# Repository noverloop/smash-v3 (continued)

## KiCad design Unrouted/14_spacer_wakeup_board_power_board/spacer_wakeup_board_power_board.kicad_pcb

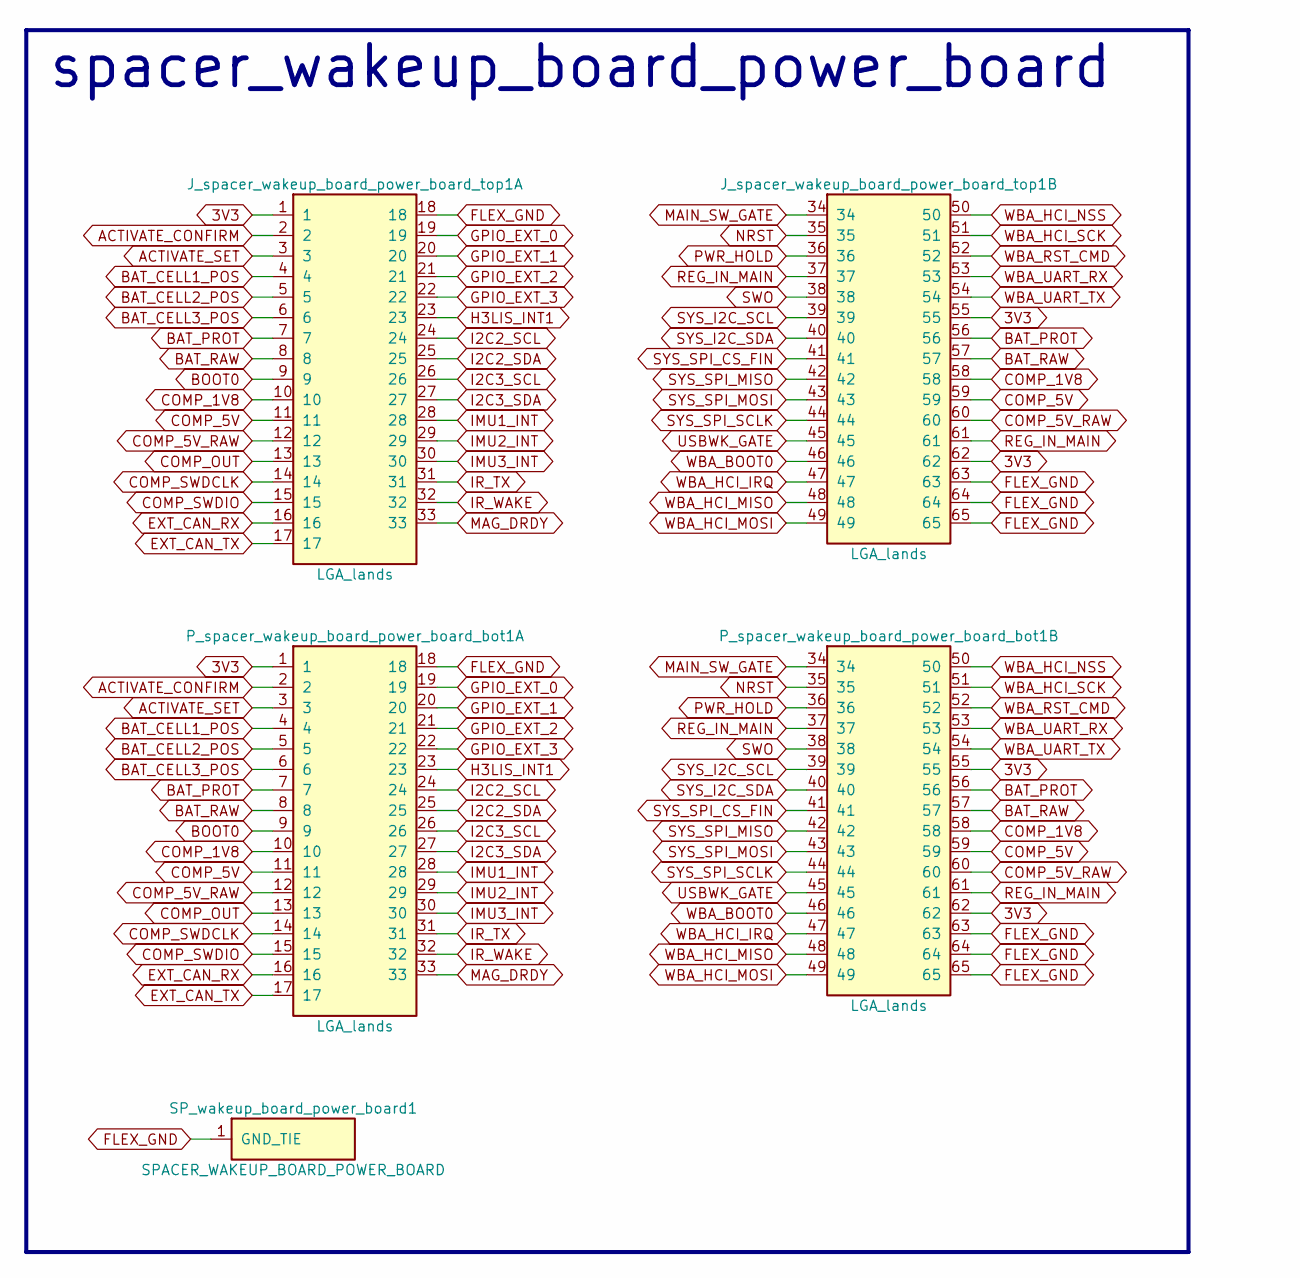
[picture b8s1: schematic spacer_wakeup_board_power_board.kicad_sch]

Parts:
J_spacer_wakeup_board_power_board_top1: LGA_lands; J_spacer_wakeup_board_power_board_top; MPN LGA_lands
P_spacer_wakeup_board_power_board_bot1: LGA_lands; P_spacer_wakeup_board_power_board_bot; MPN LGA_lands
SP_wakeup_board_power_board1: SPACER_WAKEUP_BOARD_POWER_BOARD; Spacer_Mechanical_34mm

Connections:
3V3: J_spacer_wakeup_board_power_board_top1.1, J_spacer_wakeup_board_power_board_top1.55, J_spacer_wakeup_board_power_board_top1.62, P_spacer_wakeup_board_power_board_bot1.1, P_spacer_wakeup_board_power_board_bot1.55, P_spacer_wakeup_board_power_board_bot1.62
ACTIVATE_CONFIRM: J_spacer_wakeup_board_power_board_top1.2, P_spacer_wakeup_board_power_board_bot1.2
ACTIVATE_SET: J_spacer_wakeup_board_power_board_top1.3, P_spacer_wakeup_board_power_board_bot1.3
BAT_CELL1_POS: J_spacer_wakeup_board_power_board_top1.4, P_spacer_wakeup_board_power_board_bot1.4
BAT_CELL2_POS: J_spacer_wakeup_board_power_board_top1.5, P_spacer_wakeup_board_power_board_bot1.5
BAT_CELL3_POS: J_spacer_wakeup_board_power_board_top1.6, P_spacer_wakeup_board_power_board_bot1.6
BAT_PROT: J_spacer_wakeup_board_power_board_top1.7, J_spacer_wakeup_board_power_board_top1.56, P_spacer_wakeup_board_power_board_bot1.7, P_spacer_wakeup_board_power_board_bot1.56
BAT_RAW: J_spacer_wakeup_board_power_board_top1.8, J_spacer_wakeup_board_power_board_top1.57, P_spacer_wakeup_board_power_board_bot1.8, P_spacer_wakeup_board_power_board_bot1.57
BOOT0: J_spacer_wakeup_board_power_board_top1.9, P_spacer_wakeup_board_power_board_bot1.9
COMP_1V8: J_spacer_wakeup_board_power_board_top1.10, J_spacer_wakeup_board_power_board_top1.58, P_spacer_wakeup_board_power_board_bot1.10, P_spacer_wakeup_board_power_board_bot1.58
COMP_5V: J_spacer_wakeup_board_power_board_top1.11, J_spacer_wakeup_board_power_board_top1.59, P_spacer_wakeup_board_power_board_bot1.11, P_spacer_wakeup_board_power_board_bot1.59
COMP_5V_RAW: J_spacer_wakeup_board_power_board_top1.12, J_spacer_wakeup_board_power_board_top1.60, P_spacer_wakeup_board_power_board_bot1.12, P_spacer_wakeup_board_power_board_bot1.60
COMP_OUT: J_spacer_wakeup_board_power_board_top1.13, P_spacer_wakeup_board_power_board_bot1.13
COMP_SWDCLK: J_spacer_wakeup_board_power_board_top1.14, P_spacer_wakeup_board_power_board_bot1.14
COMP_SWDIO: J_spacer_wakeup_board_power_board_top1.15, P_spacer_wakeup_board_power_board_bot1.15
EXT_CAN_RX: J_spacer_wakeup_board_power_board_top1.16, P_spacer_wakeup_board_power_board_bot1.16
EXT_CAN_TX: J_spacer_wakeup_board_power_board_top1.17, P_spacer_wakeup_board_power_board_bot1.17
FLEX_GND: J_spacer_wakeup_board_power_board_top1.18, J_spacer_wakeup_board_power_board_top1.63, J_spacer_wakeup_board_power_board_top1.64, J_spacer_wakeup_board_power_board_top1.65, P_spacer_wakeup_board_power_board_bot1.18, P_spacer_wakeup_board_power_board_bot1.63, P_spacer_wakeup_board_power_board_bot1.64, P_spacer_wakeup_board_power_board_bot1.65, SP_wakeup_board_power_board1.1
GPIO_EXT_0: J_spacer_wakeup_board_power_board_top1.19, P_spacer_wakeup_board_power_board_bot1.19
GPIO_EXT_1: J_spacer_wakeup_board_power_board_top1.20, P_spacer_wakeup_board_power_board_bot1.20
GPIO_EXT_2: J_spacer_wakeup_board_power_board_top1.21, P_spacer_wakeup_board_power_board_bot1.21
GPIO_EXT_3: J_spacer_wakeup_board_power_board_top1.22, P_spacer_wakeup_board_power_board_bot1.22
H3LIS_INT1: J_spacer_wakeup_board_power_board_top1.23, P_spacer_wakeup_board_power_board_bot1.23
I2C2_SCL: J_spacer_wakeup_board_power_board_top1.24, P_spacer_wakeup_board_power_board_bot1.24
I2C2_SDA: J_spacer_wakeup_board_power_board_top1.25, P_spacer_wakeup_board_power_board_bot1.25
I2C3_SCL: J_spacer_wakeup_board_power_board_top1.26, P_spacer_wakeup_board_power_board_bot1.26
I2C3_SDA: J_spacer_wakeup_board_power_board_top1.27, P_spacer_wakeup_board_power_board_bot1.27
IMU1_INT: J_spacer_wakeup_board_power_board_top1.28, P_spacer_wakeup_board_power_board_bot1.28
IMU2_INT: J_spacer_wakeup_board_power_board_top1.29, P_spacer_wakeup_board_power_board_bot1.29
IMU3_INT: J_spacer_wakeup_board_power_board_top1.30, P_spacer_wakeup_board_power_board_bot1.30
IR_TX: J_spacer_wakeup_board_power_board_top1.31, P_spacer_wakeup_board_power_board_bot1.31
IR_WAKE: J_spacer_wakeup_board_power_board_top1.32, P_spacer_wakeup_board_power_board_bot1.32
MAG_DRDY: J_spacer_wakeup_board_power_board_top1.33, P_spacer_wakeup_board_power_board_bot1.33
MAIN_SW_GATE: J_spacer_wakeup_board_power_board_top1.34, P_spacer_wakeup_board_power_board_bot1.34
NRST: J_spacer_wakeup_board_power_board_top1.35, P_spacer_wakeup_board_power_board_bot1.35
PWR_HOLD: J_spacer_wakeup_board_power_board_top1.36, P_spacer_wakeup_board_power_board_bot1.36
REG_IN_MAIN: J_spacer_wakeup_board_power_board_top1.37, J_spacer_wakeup_board_power_board_top1.61, P_spacer_wakeup_board_power_board_bot1.37, P_spacer_wakeup_board_power_board_bot1.61
SWO: J_spacer_wakeup_board_power_board_top1.38, P_spacer_wakeup_board_power_board_bot1.38
SYS_I2C_SCL: J_spacer_wakeup_board_power_board_top1.39, P_spacer_wakeup_board_power_board_bot1.39
SYS_I2C_SDA: J_spacer_wakeup_board_power_board_top1.40, P_spacer_wakeup_board_power_board_bot1.40
SYS_SPI_CS_FIN: J_spacer_wakeup_board_power_board_top1.41, P_spacer_wakeup_board_power_board_bot1.41
SYS_SPI_MISO: J_spacer_wakeup_board_power_board_top1.42, P_spacer_wakeup_board_power_board_bot1.42
SYS_SPI_MOSI: J_spacer_wakeup_board_power_board_top1.43, P_spacer_wakeup_board_power_board_bot1.43
SYS_SPI_SCLK: J_spacer_wakeup_board_power_board_top1.44, P_spacer_wakeup_board_power_board_bot1.44
USBWK_GATE: J_spacer_wakeup_board_power_board_top1.45, P_spacer_wakeup_board_power_board_bot1.45
WBA_BOOT0: J_spacer_wakeup_board_power_board_top1.46, P_spacer_wakeup_board_power_board_bot1.46
WBA_HCI_IRQ: J_spacer_wakeup_board_power_board_top1.47, P_spacer_wakeup_board_power_board_bot1.47
WBA_HCI_MISO: J_spacer_wakeup_board_power_board_top1.48, P_spacer_wakeup_board_power_board_bot1.48
WBA_HCI_MOSI: J_spacer_wakeup_board_power_board_top1.49, P_spacer_wakeup_board_power_board_bot1.49
WBA_HCI_NSS: J_spacer_wakeup_board_power_board_top1.50, P_spacer_wakeup_board_power_board_bot1.50
WBA_HCI_SCK: J_spacer_wakeup_board_power_board_top1.51, P_spacer_wakeup_board_power_board_bot1.51
WBA_RST_CMD: J_spacer_wakeup_board_power_board_top1.52, P_spacer_wakeup_board_power_board_bot1.52
WBA_UART_RX: J_spacer_wakeup_board_power_board_top1.53, P_spacer_wakeup_board_power_board_bot1.53
WBA_UART_TX: J_spacer_wakeup_board_power_board_top1.54, P_spacer_wakeup_board_power_board_bot1.54

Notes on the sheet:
spacer_wakeup_board_power_board

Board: 2 copper layers, 5 parts (1 on the bottom side), 54 nets, no tracks yet.

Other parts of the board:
MH1, MH2: smash_mech_potting
